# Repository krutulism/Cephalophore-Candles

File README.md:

# Ladder-LEDs
KiCAD 7 files for a chainable PCB of individually addressable LEDs.

## Abstract
Strips of individually addressable LEDs are a popular and versatile gadget. Here I develop my own degree of craftsmanship beyond the adhesive strips they often come packaged on.

I used Molex connectors to chain together rigid fiberglass PCBs. The 'housing' that motivates the shape of the PCBs is the empty rungs of a salvaged aluminum extension ladder.

## Decision Tree
In each cut-off rung I will install a custom PCB designed in KiCAD.

The individually addressable LEDs I will use are the IN-PI55QATPRPGPBPW-40 RGBW shift register LEDs from Inolux.

The connector ecosystem that will allow me to chain these boards together are the Molex Nanofit system.

I will attempt to use a screw terminal block to mount the boards.

The prototype controller will be an Arduino Uno or Nano.

I will solder the surface mount components to the board by upgrading an IR reflow oven.

## First Demo
[Test program video (Google photos link)](https://photos.app.goo.gl/88sZqstjhHEQxjQ36)

## Instructions
To correct the paths to 3D models of custom library components: select a footprint in the PCB editor, edit its properties in the right click context menu or by pressing the E key, and enter the "3D Models" tab

CAD models I derived from datasheet drawings are included. CAD models I downloaded from the manufacturer can be downloaded from manufacturer websites.

## Questions
My Arduino firmware treats these LEDs as SK6812RGBW LEDs, a common hobbyist standard. However, here is a table of data transmission times for SK6812s accessed at Adafruit:

and here is the table for the Inolux IN-PI55QATPRPGPBPW-40 LEDs I used

In scrubbing through the source libraries for [Adafruit Neopixel](https://github.com/adafruit/Adafruit_NeoPixel), which is used in my demo, I did not find where these transmission times are encoded. This leaves me wondering where my elision will break down, whether after adding more LEDs to the chain, or under a greater frequency of intensity change commands. I will keep scrubbing the source code to understand, but suggestions are welcome.

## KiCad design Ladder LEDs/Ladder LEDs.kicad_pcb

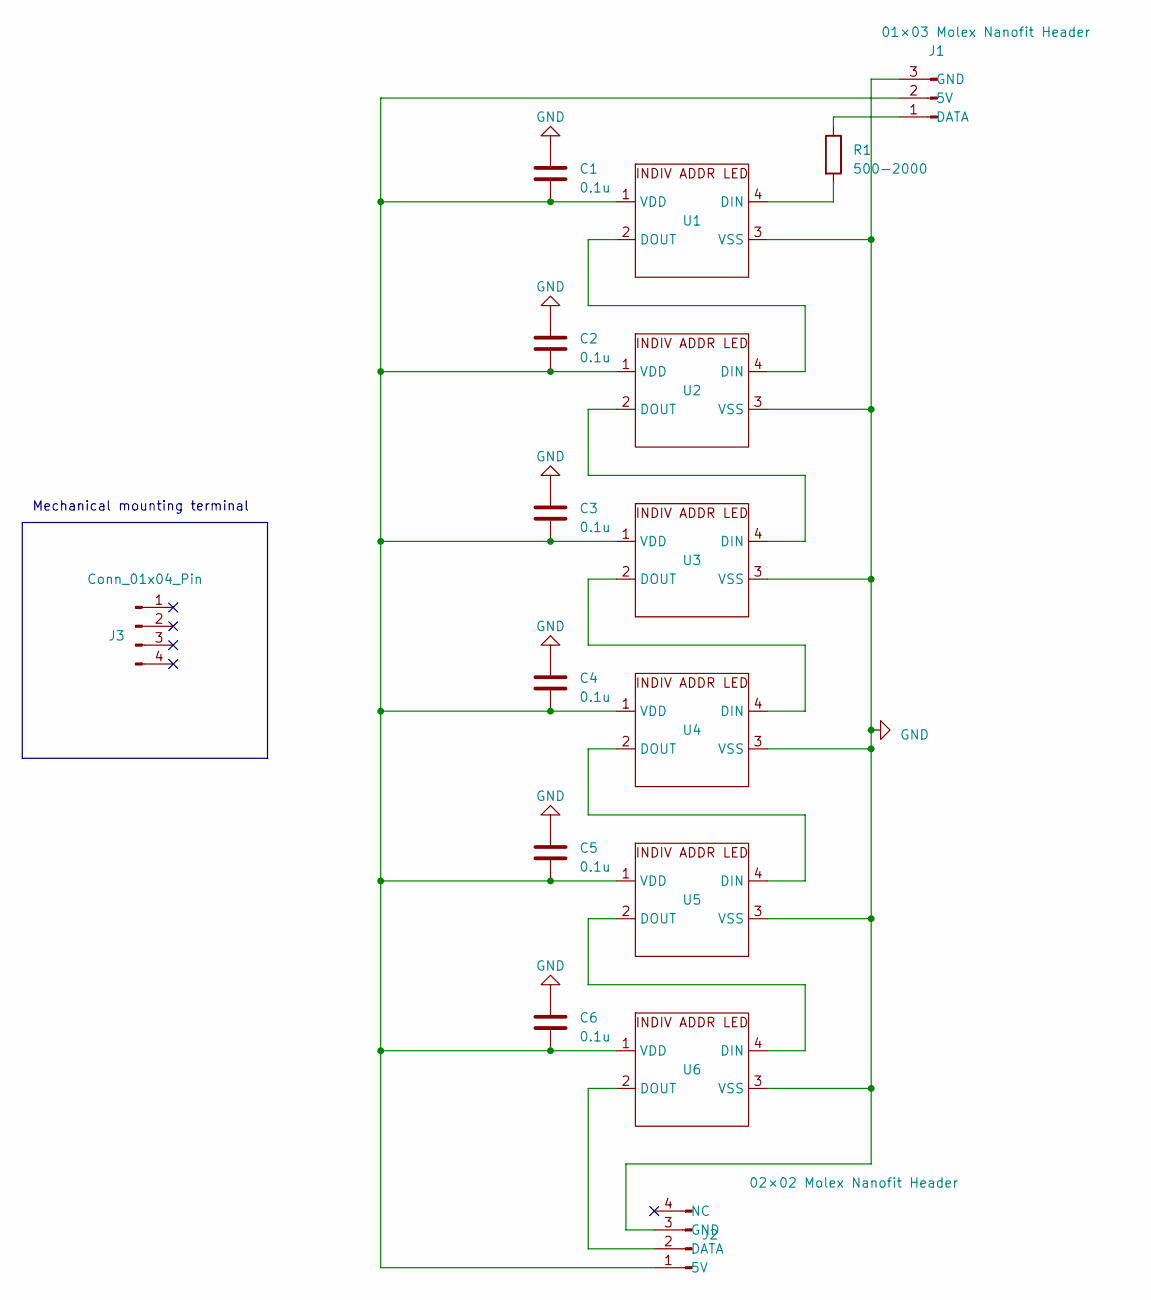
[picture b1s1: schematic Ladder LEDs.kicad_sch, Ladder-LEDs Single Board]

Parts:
C1, C2, C3, C4, C5, C6: 0.1u; C_0805_2012Metric_Pad1.18x1.45mm_HandSolder
J1: 01×03 Molex Nanofit Header; Molex 1054302103; MPN 1054302103
J2: 02×02 Molex Nanofit Header; Molex 105405-1104; MPN 1054051104
J3: Conn_01x04_Pin; 36-7773-ND; MPN 7773
R1: 500-2000; R_0805_2012Metric_Pad1.20x1.40mm_HandSolder
U1, U2, U3, U4, U5, U6: IN-PI55QATPRPGPBPW-XX

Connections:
GND: C1.1, C2.1, C3.1, C4.1, C5.1, C6.1, J1.3 (GND), J2.3 (GND), U1.3 (VSS), U2.3 (VSS), U3.3 (VSS), U4.3 (VSS), U5.3 (VSS), U6.3 (VSS)
unnamed: C1.2, C2.2, C3.2, C4.2, C5.2, C6.2, J1.2 (5V), J2.1 (5V), U1.1 (VDD), U2.1 (VDD), U3.1 (VDD), U4.1 (VDD), U5.1 (VDD), U6.1 (VDD)
unnamed: J1.1 (DATA), R1.1
unnamed: J2.2 (DATA), U6.2 (DOUT)
unnamed: R1.2, U1.4 (DIN)
unnamed: U1.2 (DOUT), U2.4 (DIN)
unnamed: U2.2 (DOUT), U3.4 (DIN)
unnamed: U3.2 (DOUT), U4.4 (DIN)
unnamed: U4.2 (DOUT), U5.4 (DIN)
unnamed: U5.2 (DOUT), U6.4 (DIN)

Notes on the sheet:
Mechanical mounting terminal

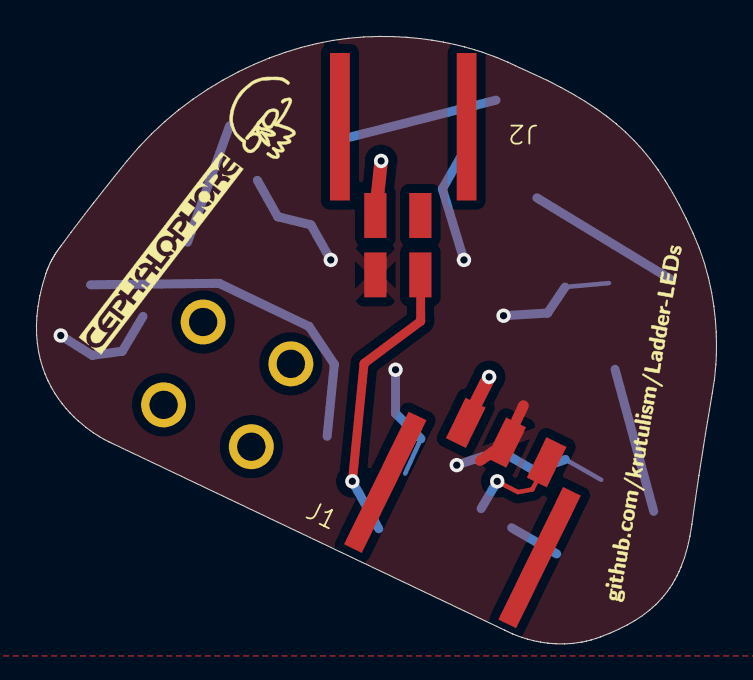
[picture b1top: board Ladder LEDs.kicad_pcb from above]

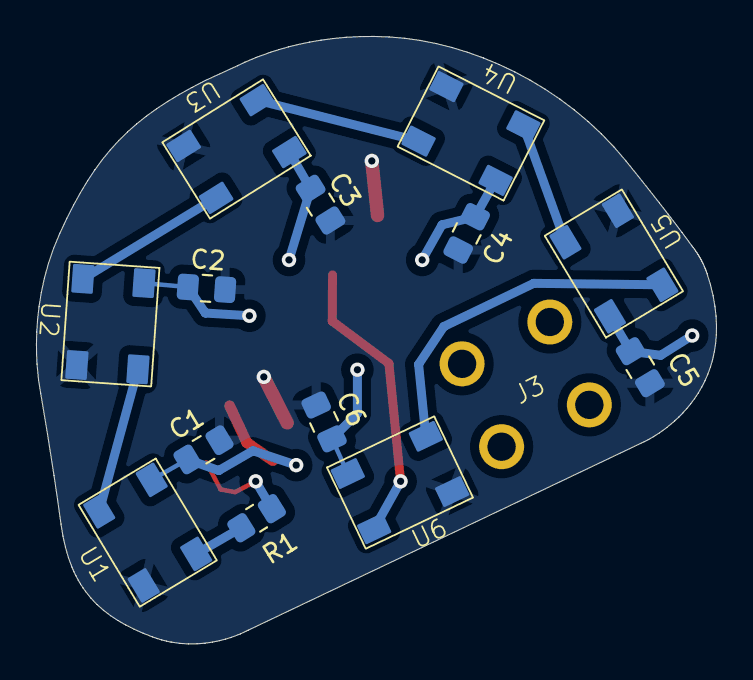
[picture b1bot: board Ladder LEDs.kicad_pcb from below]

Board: 2 copper layers, 37.8 x 33.7 mm, 16 parts (13 on the bottom side), 10 nets.

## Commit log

2023-03-21 Imported v1 KiCAD files
2023-03-22 Created Gerber files for OSH Park
2023-03-29 Populated README
2023-03-29 Placed Gerber files in folder
2023-03-29 Renamed project, ignored backups
2023-03-29 Updated .gitignore
2023-04-25 Trimmed BOM, added 3D models
2023-04-25 Corrected .gitignore
2023-04-25 Troubleshooting gitignore
2023-09-05 Added images, trying image embed
2023-09-05 Added data tables and video
2023-09-05 Healed md image embeds
2023-09-05 Fixed more md embeds
2023-09-05 Troubleshooting md
2023-09-05 Additional image in readme
2023-09-05 Editing readme
2023-09-06 Edited readme
